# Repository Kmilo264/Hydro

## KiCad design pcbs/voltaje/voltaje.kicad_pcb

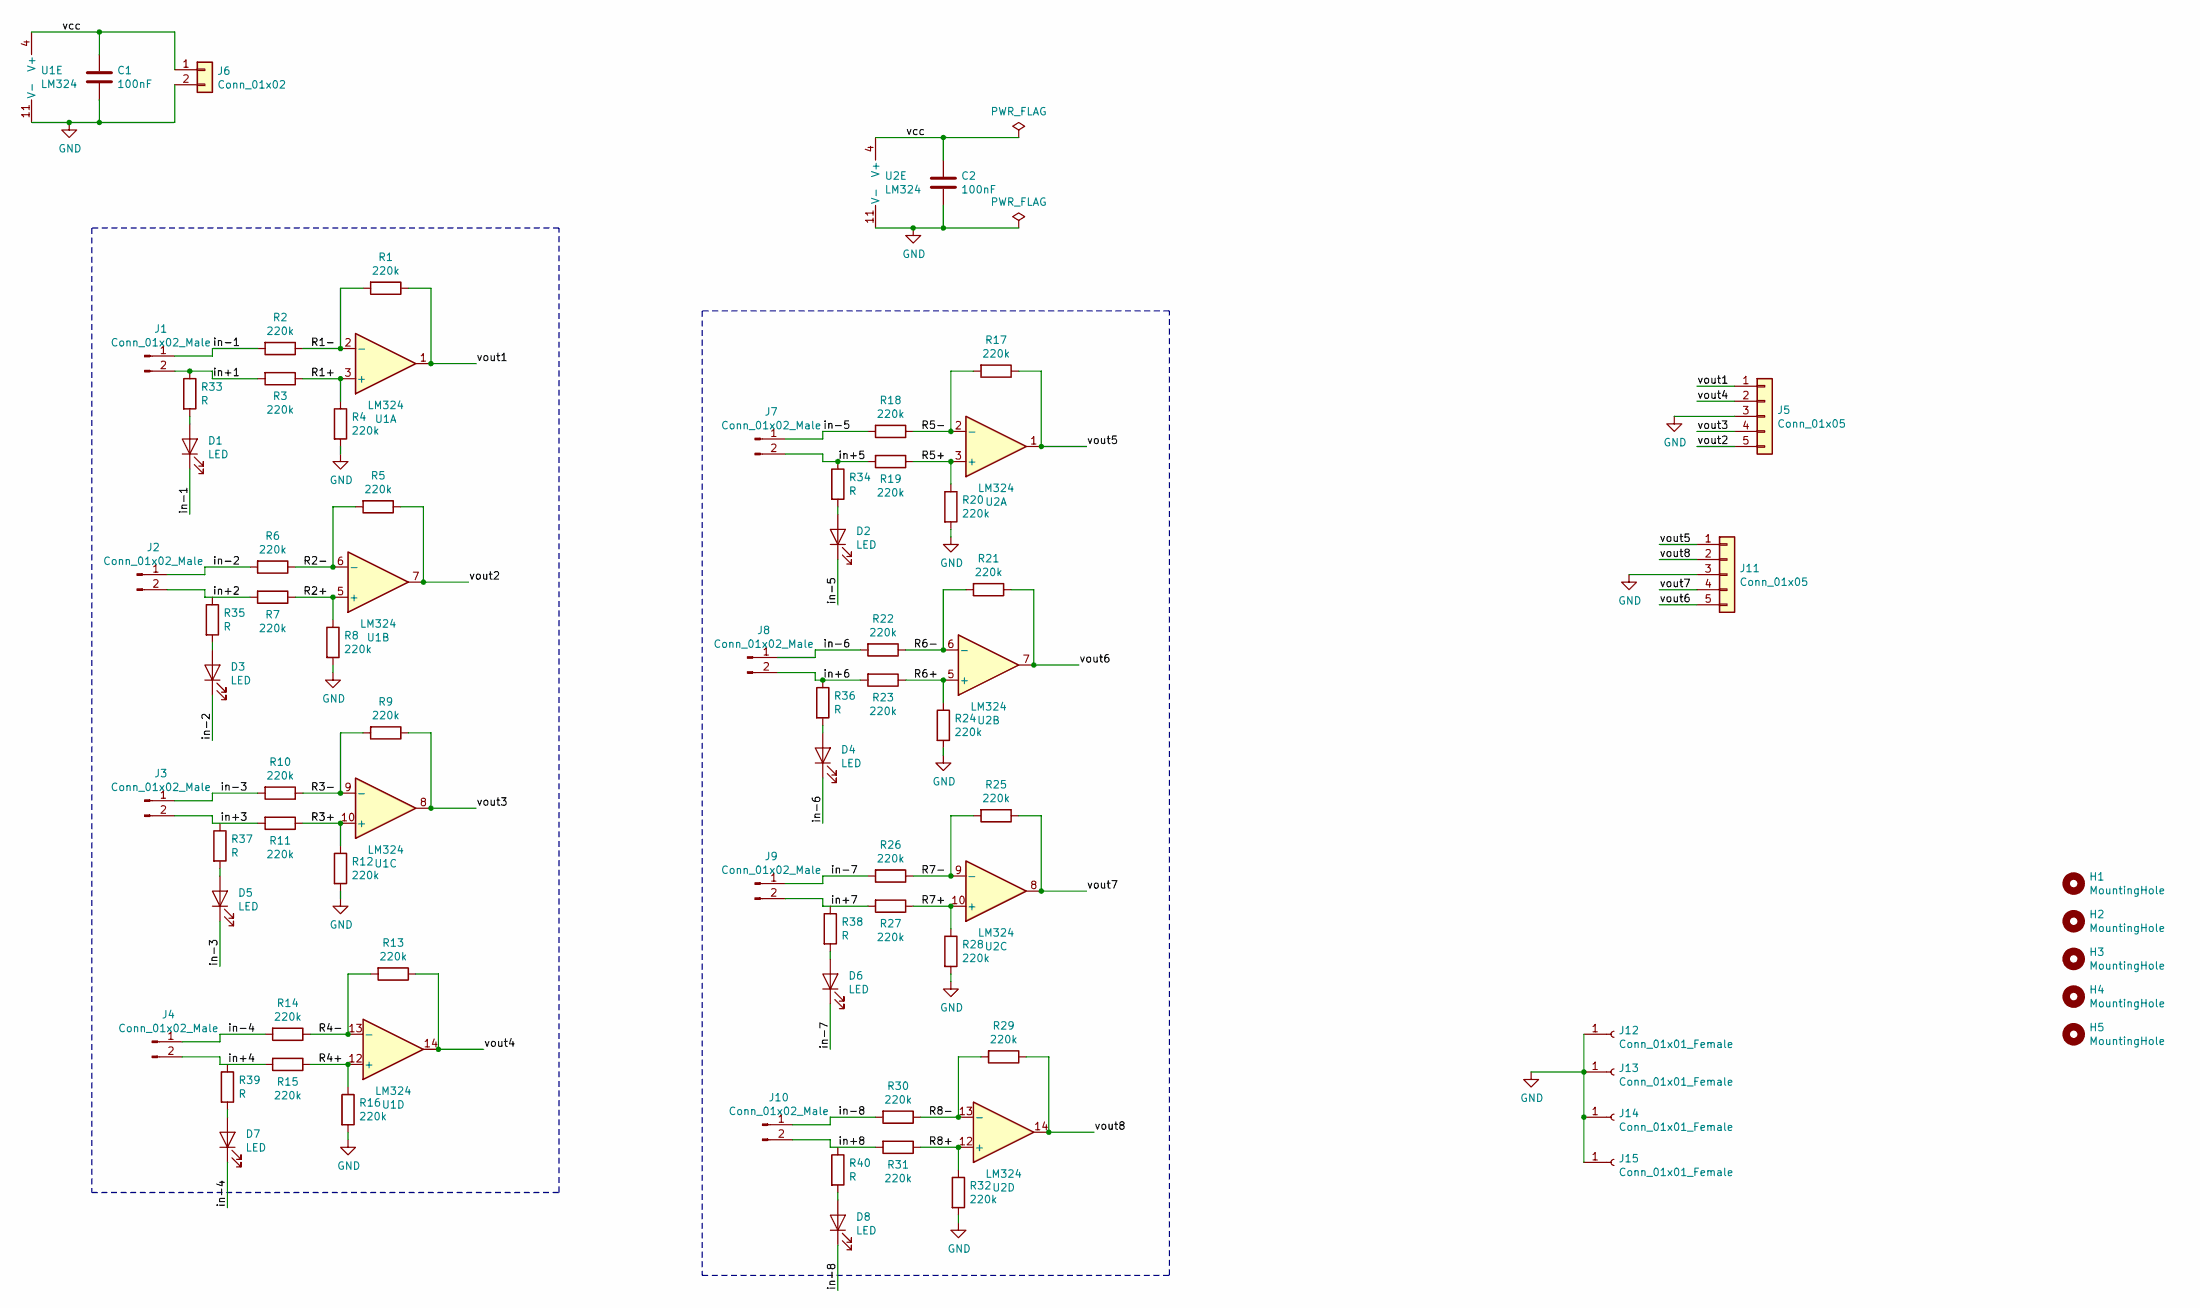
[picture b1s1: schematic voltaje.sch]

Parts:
C1, C2: 100nF; C_0805_2012Metric_Pad1.15x1.40mm_HandSolder
D1, D2, D3, D4, D5, D6, D7, D8: LED; LED_D3.0mm_Clear
H1, H2, H3, H4, H5: MountingHole; MountingHole_3.5mm
J1, J2, J3, J4, J7, J8, J9, J10: Conn_01x02_Male; Molex_KK-254_AE-6410-02A_1x02_P2.54mm_Vertical
J5, J11: Conn_01x05; PinHeader_1x05_P2.54mm_Vertical
J6: Conn_01x02; Molex_KK-254_AE-6410-02A_1x02_P2.54mm_Vertical
J12, J13, J14, J15: Conn_01x01_Female; PinHeader_1x01_P2.54mm_Vertical
R1, R2, R3, R4, R5, R6, R7, R8, R9, R10, R11, R12, R13, R14, R15, R16, R17, R18, R19, R20, R21, R22, R23, R24, R25, R26, R27, R28, R29, R30, R31, R32: 220k; R_Axial_DIN0207_L6.3mm_D2.5mm_P7.62mm_Horizontal
R33, R34, R35, R36, R37, R38, R39, R40: R; R_Axial_DIN0207_L6.3mm_D2.5mm_P7.62mm_Horizontal
U1, U2: LM324; DIP-14_W7.62mm

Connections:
/R1+: R3.1, R4.1, U1.3 (+)
/R1-: R1.2, R2.1, U1.2 (-)
/R2+: R7.1, R8.1, U1.5 (+)
/R2-: R5.2, R6.1, U1.6 (-)
/R3+: R11.1, R12.1, U1.10 (+)
/R3-: R9.2, R10.1, U1.9 (-)
/R4+: R15.1, R16.1, U1.12 (+)
/R4-: R13.2, R14.1, U1.13 (-)
/R5+: R19.1, R20.1, U2.3 (+)
/R5-: R17.2, R18.1, U2.2 (-)
/R6+: R23.1, R24.1, U2.5 (+)
/R6-: R21.2, R22.1, U2.6 (-)
/R7+: R27.1, R28.1, U2.10 (+)
/R7-: R25.2, R26.1, U2.9 (-)
/R8+: R31.1, R32.1, U2.12 (+)
/R8-: R29.2, R30.1, U2.13 (-)
/in+1: J1.2, R3.2, R33.1
/in+2: J2.2, R7.2, R35.1
/in+3: J3.2, R11.2, R37.1
/in+4: J4.2, R15.2, R39.1
/in+5: J7.2, R19.2, R34.1
/in+6: J8.2, R23.2, R36.1
/in+7: J9.2, R27.2, R38.1
/in+8: J10.2, R31.2, R40.1
/in-1: D1.1 (K), J1.1, R2.2
/in-2: D3.1 (K), J2.1, R6.2
/in-3: D5.1 (K), J3.1, R10.2
/in-4: D7.1 (K), J4.1, R14.2
/in-5: D2.1 (K), J7.1, R18.2
/in-6: D4.1 (K), J8.1, R22.2
/in-7: D6.1 (K), J9.1, R26.2
/in-8: D8.1 (K), J10.1, R30.2
/vcc: C1.1, C2.1, J6.1, U1.4 (V+), U2.4 (V+)
/vout1: J5.1, R1.1, U1.1
/vout2: J5.5, R5.1, U1.7
/vout3: J5.4, R9.1, U1.8
/vout4: J5.2, R13.1, U1.14
/vout5: J11.1, R17.1, U2.1
/vout6: J11.5, R21.1, U2.7
/vout7: J11.4, R25.1, U2.8
/vout8: J11.2, R29.1, U2.14
GND: C1.2, C2.2, J5.3, J6.2, J11.3, J12.1, J13.1, J14.1, J15.1, R4.2, R8.2, R12.2, R16.2, R20.2, R24.2, R28.2, R32.2, U1.11 (V-), U2.11 (V-)
unnamed: D1.2 (A), R33.2
unnamed: D2.2 (A), R34.2
unnamed: D3.2 (A), R35.2
unnamed: D4.2 (A), R36.2
unnamed: D5.2 (A), R37.2
unnamed: D6.2 (A), R38.2
unnamed: D7.2 (A), R39.2
unnamed: D8.2 (A), R40.2

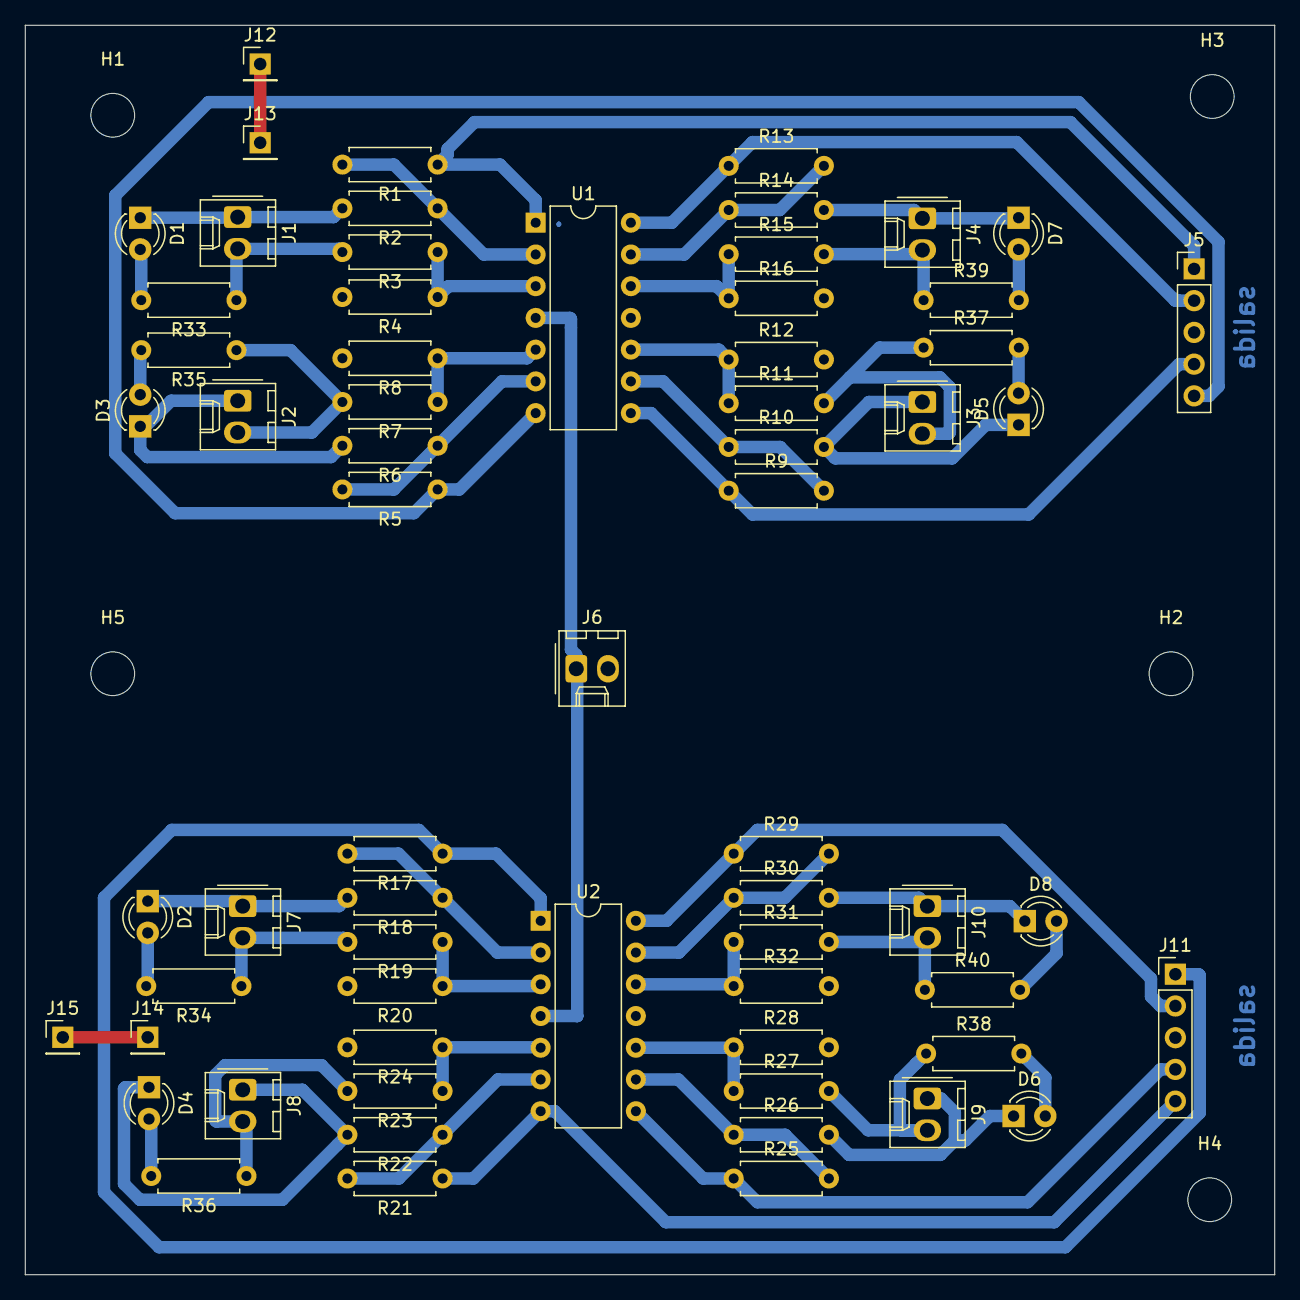
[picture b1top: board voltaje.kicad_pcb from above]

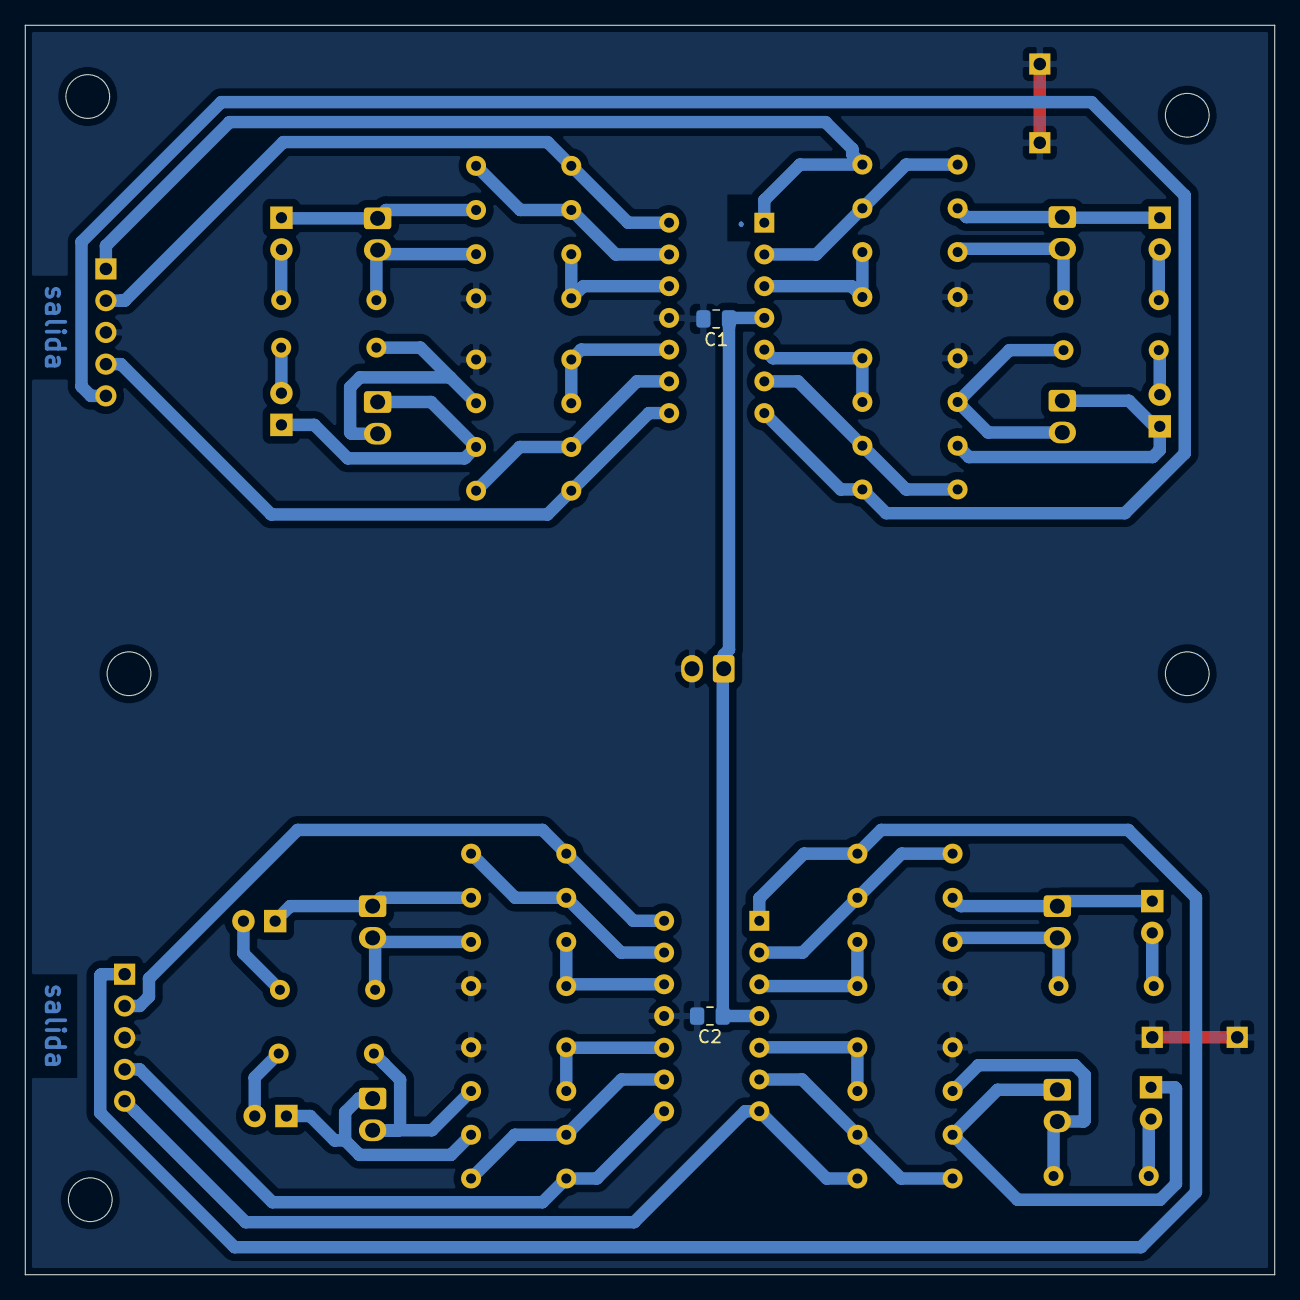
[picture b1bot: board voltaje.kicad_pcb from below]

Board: 2 copper layers, 100.0 x 100.0 mm, 72 parts (2 on the bottom side), 50 nets.

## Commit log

2019-12-14 Interfaz pits
2019-12-14 Lee y grafica los datos de ambos acelerómetros. La trama ahora termina con un final de línea.
2019-12-14 Velocidad
2019-12-15 Al graficar x, y ahora tienen la misma dimensión.
2019-12-15 funciona boton limpiar además ahora se grafica la velocidad
2019-12-15 Separadas las gráficas para los acelerómetros
2019-12-15 Agregado widget de inclinación
2019-12-15 A máxima velocidad no se bloquea
2019-12-15 Limita la cantidad de puntos almacenados en la lista.
2019-12-15 Permite cambiar la velocidad
2019-12-16 PCB medir voltaje de las celdas
2020-02-18 Grafica todos los datos
